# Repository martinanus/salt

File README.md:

# Proyecto SALT 

### Resumen
Este trabajo presenta el diseño e implementación de un prototipo para un sistema de aislado limitado total para formaciones ferroviarias (SAL/T) basado en un pliego de especificaciones de la empresa Trenes Argentinos Operaciones y en una primera versión del prototipo realizado anteriormente en el contexto del Grupo de Investigación en Calidad y Seguridad de las Aplicaciones Ferroviarias (GICSAFe). En esta versión, se agregan nuevas funcionalidades, se actualiza el hardware utilizado y se mejora la portabilidad de su firmware.     

Este sistema permite aumentar la seguridad de los trenes ante una falla en alguno de sus sistemas instrumentados de seguridad interfiriendo las señales de corte de tracción y freno de emergencia de la formación y aislando el subsistema en fallo. El SAL/T considera múltiples fuentes de medición de la velocidad de la formación y la comunicación con una central operativa para determinar cómo debe intervenir estas señales críticas para llevar a la formación a un estado seguro de manera controlada.

### Diagrama en bloques del SAL/T

### Diseño del panel frontal del sistema

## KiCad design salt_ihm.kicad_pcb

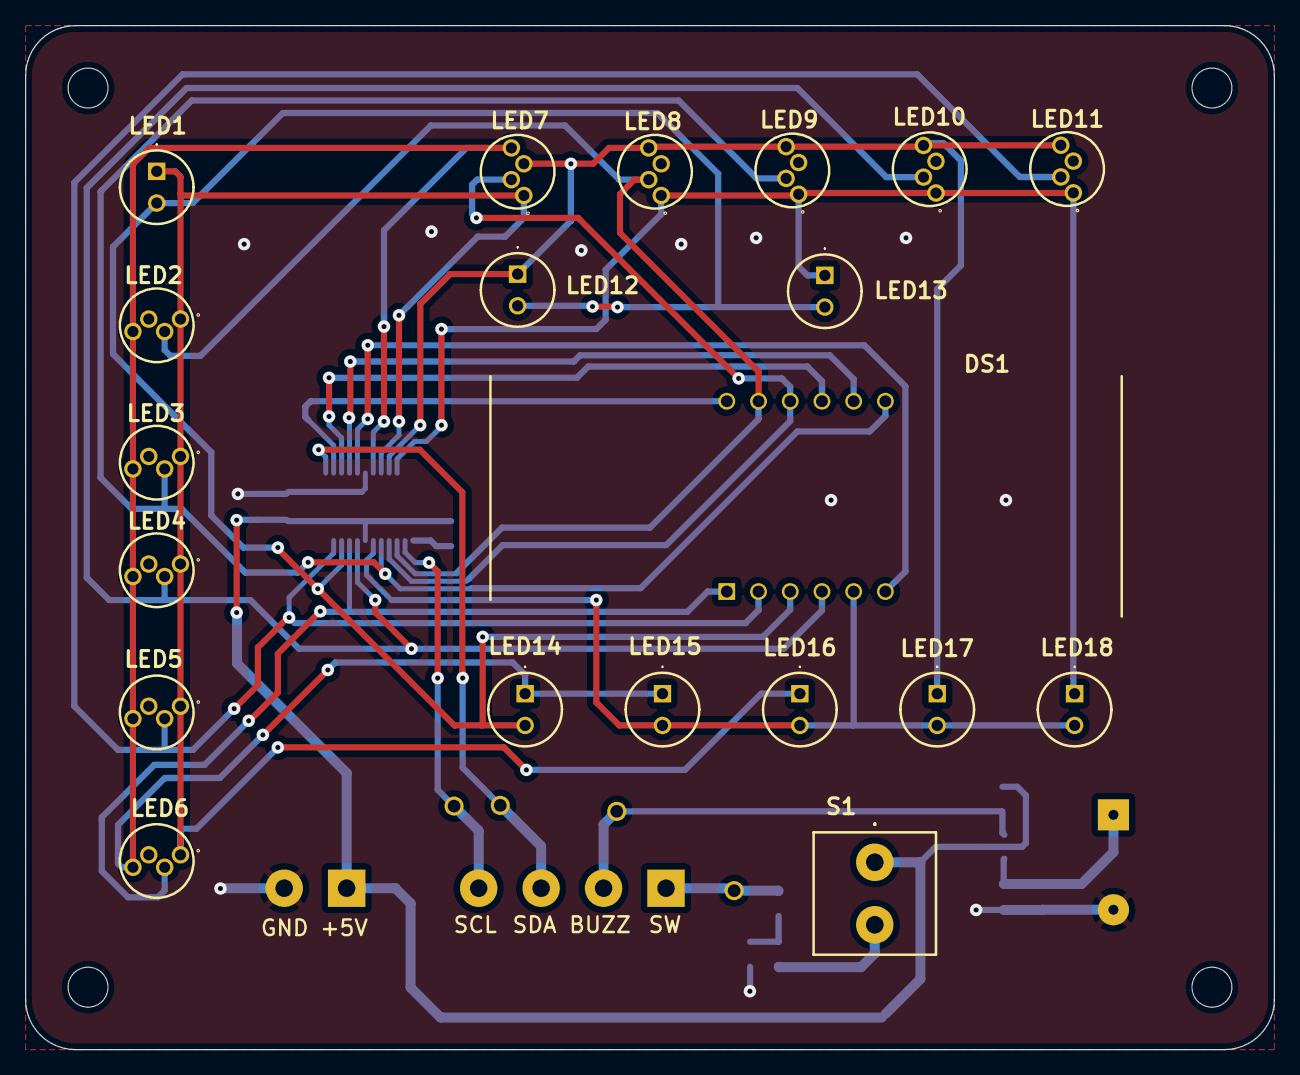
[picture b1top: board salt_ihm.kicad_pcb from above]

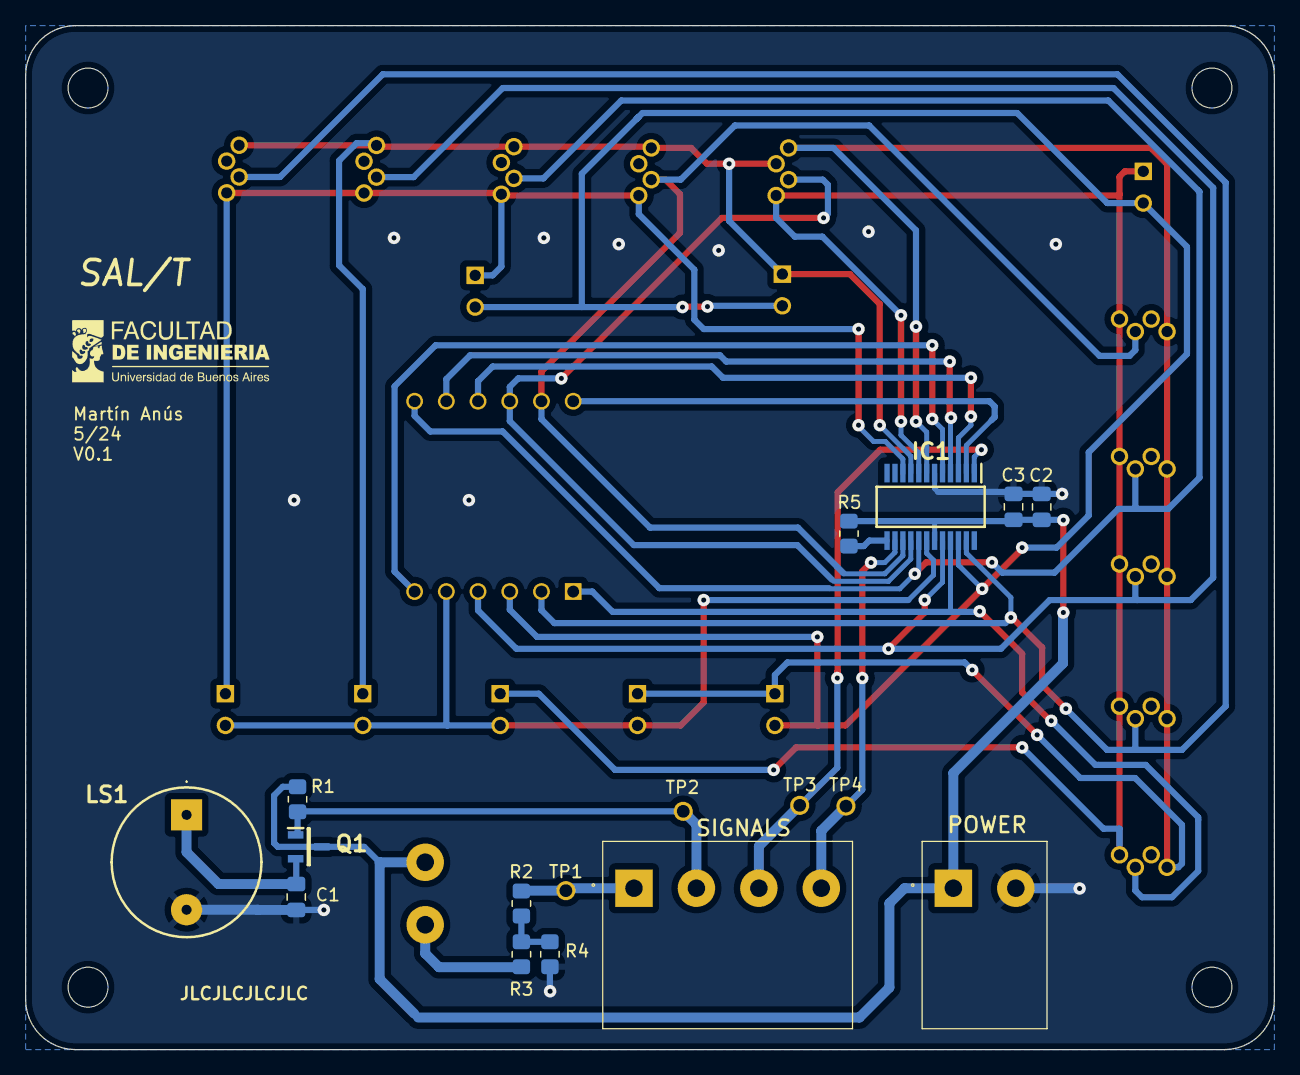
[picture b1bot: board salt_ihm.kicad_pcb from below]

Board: 2 copper layers, 100.0 x 82.0 mm, 41 parts (17 on the bottom side), 26 nets.

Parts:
C1, C2: 10uF; C_0805_2012Metric_Pad1.18x1.45mm_HandSolder
C3: 100nF; C_0805_2012Metric_Pad1.18x1.45mm_HandSolder
DS1: LTC-5723HR; DIP1524W75P254L5030H825Q12N
H1, H2, H3, H4: MountingHole; MountingHole_3.2mm_M3
IC1: AS1115-BSST; SOP64P600X175-24N
J1: 1934861
J2: 1934887
LED1, LED12, LED13, LED14, LED15, LED16, LED17, LED18: WP7113LZGCK
LED2, LED3, LED4, LED5, LED6, LED7, LED8, LED9, LED10, LED11: WP154A4SEJ3VBDZGW_CA; L-154A4SUREQBFZGEC
LS1: CEM-1205-IC; CEM1205IC
Q1: NVTR0202PLT1G; SOT96P237X111-3N
R1: 150k; R_0805_2012Metric_Pad1.20x1.40mm_HandSolder
R2: 100; R_0805_2012Metric_Pad1.20x1.40mm_HandSolder
R3, R5: 22k; R_0805_2012Metric_Pad1.20x1.40mm_HandSolder
R4: 40K2; R_0805_2012Metric_Pad1.20x1.40mm_HandSolder
S1: 1543-650-149; 1543650149
TP1, TP2, TP3, TP4: TestPoint; testpoint

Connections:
+5V: C2.1, C3.1, IC1.19 (VDD), J1.1, Q1.3 (D), R1.1, R5.1, S1.1
/A_A: DS1.11 (A_A), IC1.15 (SEGA), LED2.2 (COMMON_ANODE), LED8.2 (COMMON_ANODE)
/A_B: DS1.7 (A_B), IC1.17 (SEGB), LED3.2 (COMMON_ANODE), LED9.2 (COMMON_ANODE)
/A_C: DS1.4 (A_C), IC1.20 (SEGC), LED4.2 (COMMON_ANODE), LED10.2 (COMMON_ANODE)
/A_D: DS1.2 (A_D), IC1.23 (SEGD), LED5.2 (COMMON_ANODE), LED11.2 (COMMON_ANODE)
/A_DP: DS1.3 (A_D.P.), IC1.22 (SEGDP), LED1.2 (A), LED12.2 (A), LED13.2 (A), LED14.2 (A)
/A_E: DS1.1 (A_E), IC1.21 (SEG_E), LED6.2 (COMMON_ANODE)
/A_F: DS1.10 (A_F), IC1.16 (SEGF), LED7.2 (COMMON_ANODE)
/A_G: DS1.5 (A_G), IC1.18 (SEGG), LED15.2 (A), LED16.2 (A), LED17.2 (A), LED18.2 (A)
/BUZZER_C: J2.2, Q1.1 (G), R1.2, TP2.1
/CC_0: DS1.12 (COMMON_K_(DIGIT_1)), IC1.2 (DIG0)
/CC_1: DS1.9 (COMMON_K_(DIGIT_2)), IC1.3 (DIG1)
/CC_2: DS1.8 (COMMON_K_(DIGIT_3)), IC1.4 (DIG2)
/CC_3: DS1.6 (COMMON_K_(DIGIT_4)), IC1.5 (DIG3)
/CC_4: IC1.7 (DIG4), LED2.4 (GREEN_CATHODE), LED3.4 (GREEN_CATHODE), LED4.4 (GREEN_CATHODE), LED5.4 (GREEN_CATHODE), LED6.4 (GREEN_CATHODE), LED7.4 (GREEN_CATHODE), LED14.1 (K), LED15.1 (K)
/CC_5: IC1.8 (DIG5), LED1.1 (K), LED2.1 (RED_CATHODE), LED3.1 (RED_CATHODE), LED4.1 (RED_CATHODE), LED5.1 (RED_CATHODE), LED6.1 (RED_CATHODE), LED7.1 (RED_CATHODE), LED16.1 (K)
/CC_6: IC1.9 (DIG6), LED7.3 (BLUE_CATHODE), LED8.4 (GREEN_CATHODE), LED9.4 (GREEN_CATHODE), LED10.4 (GREEN_CATHODE), LED11.4 (GREEN_CATHODE), LED12.1 (K), LED17.1 (K)
/CC_7: IC1.10 (DIG7), LED8.1 (RED_CATHODE), LED9.1 (RED_CATHODE), LED10.1 (RED_CATHODE), LED11.1 (RED_CATHODE), LED13.1 (K), LED18.1 (K)
/CHOP_SEL: J2.1, R2.1, TP1.1
/SCL: IC1.14 (SCL), J2.4, TP4.1
/SDA: IC1.1 (SDA), J2.3, TP3.1
GND: C1.1, C2.2, C3.2, IC1.6 (GND), J1.2, LS1.2, R4.1
unnamed: C1.2, LS1.1, Q1.2 (S)
unnamed: IC1.13 (ISET), R5.2
unnamed: R2.2, R3.2, R4.2
unnamed: R3.1, S1.2

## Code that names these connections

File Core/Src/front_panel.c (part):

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    uint8_t D5_B = extractBit(SIS_leds[2], 1); // LED9_GREEN  - CC_6 - A_B  - SIS_3
    uint8_t D4_C = extractBit(SIS_leds[3], 1); // LED10_GREEN - CC_6 - A_C  - SIS_4
    uint8_t D3_D = extractBit(SIS_leds[4], 1); // LED11_GREEN - CC_6 - A_D  - SIS_5
    uint8_t D2_E = 0;                          // NC          - CC_6 - A_E  - NC
    uint8_t D1_F = extractBit(SIS_leds[0], 0); // LED7_BLUE   - CC_6 - A_F  - SIS_1-->ZONA
    uint8_t D0_G = chop_profile_leds[3];       // LED17       - CC_6 - A_G  - CHOP_4

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    uint8_t D5_B = extractBit(SIS_leds[2], 2); // LED9_RED  - CC_7 - A_B  - SIS_3
    uint8_t D4_C = extractBit(SIS_leds[3], 2); // LED10_RED - CC_7 - A_C  - SIS_4
    uint8_t D3_D = extractBit(SIS_leds[4], 2); // LED11_RED - CC_7 - A_D  - SIS_5
    uint8_t D2_E = 0;                          // NC        - CC_7 - A_E  - NC
    uint8_t D1_F = 0;                          // NC        - CC_7 - A_F  - NC
    uint8_t D0_G = chop_profile_leds[4];       // LED18     - CC_7 - A_G  - CHOP_5

    uint8_t vars[8] = {D0_G, D1_F, D2_E, D3_D, D4_C, D5_B, D6_A, D7_DP};
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
    if (buzzer_state == BUZZER_OFF)
    {
        HAL_GPIO_WritePin(BUZZER_C_GPIO_Port, BUZZER_C_Pin, 0);
        HAL_GPIO_WritePin(LD2_GPIO_Port, LD2_Pin, 0);
    }
    else if (buzzer_state == BUZZER_ON_CONTINUOS)
    {
        HAL_GPIO_WritePin(BUZZER_C_GPIO_Port, BUZZER_C_Pin, 1);
        HAL_GPIO_WritePin(LD2_GPIO_Port, LD2_Pin, 1);
    }
    else if (buzzer_state == BUZZER_ON_INTERMITENT)
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        currentMillis = HAL_GetTick();
        if (currentMillis - buzzer_toggle_ms > BUZZER_SOUND_PERIOD_S * 1000)
        {
            HAL_GPIO_TogglePin(BUZZER_C_GPIO_Port, BUZZER_C_Pin);
            HAL_GPIO_TogglePin(LD2_GPIO_Port, LD2_Pin);

            buzzer_toggle_ms = currentMillis;
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
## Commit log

2024-06-28 freeRTOS working example
2024-06-28 adc working example
2024-06-28 gps working example
2024-06-28 sd working example
2024-06-28 wifi working example
2024-06-28 integration working example
2024-06-28 first hardware principal reviewed and manufactured
2024-06-28 first hardware ihm reviewed and manufactured
2024-07-08 improves uart bidirectional communication
2024-07-08 integrates switch read, chop button int and refactor code
2024-07-08 clean build files
2024-07-28 led driver working example
2024-07-28 refactor: modularize led driver and define regs and values
2024-07-31 adds some address macros
2024-07-31 includes led_driver logic and communication
2024-07-31 working example
2024-07-31 handle salt mode transitions structure
2024-08-05 maps states to leds variables
2024-08-05 implements transition functs
2024-08-10 adds GPS module reset function
2024-08-10 adds testing relay function
2024-08-11 ads rs485 direction pin
2024-08-11 includes rs485 reading
2024-08-11 update relay enums for clarity
2024-08-11 includes relay combination states for critical signals
2024-08-15 includes critical signals setting and chop profiles timing
2024-08-18 control register relays
2024-08-18 log events when state changed
2024-08-18 includes RTC timestamps on logs
2024-08-21 use same main routine for all modes
2024-08-21 adds esp32 worjing examples
2024-08-21 retransmit datetime every 10s
2024-08-21 salt data in Serial2 pins
2024-08-21 update RTC clock from esp32 wifi messages
2024-08-25 includes RS485 reception logic
2024-08-27 display dash no speed and hide left zeros
2024-08-27 adds speed read validity time logic
2024-08-27 format user files in C style
2024-08-27 format h files
2024-08-28 read current zone from gps coordinates
2024-08-28 adds distance calculation from gps coordinates
2024-08-28 refactor speed and chop profiles for configuration
2024-08-28 allws updating speed, chop profile and command validity parameters via remote command
2024-08-28 apply command expiration
2024-08-30 includes remote salt_mode commands
2024-08-30 buzzer on intermitent in Limitado mode
2024-08-30 adds log download logic
2024-08-31 fix gps calculations
2024-08-31 fixes after commands testing
2024-08-31 implement hasler frame detection
2024-08-31 fix clearing buffer
2024-09-01 improves command receive after mqtt testing
2024-09-04 esp checks for multiple network connection
2024-09-04 adds mqtt client simulating central operativa
2024-09-04 adds ID responde in remote commands
2024-09-06 transmit ACK in separated topic
2024-09-06 adds separated topic for ACK
2024-09-06 transmit ACK msg in a different topic
2024-09-06 log status with labels
2024-09-06 adds report status period config and transmit
2024-09-06 adds STATUS topic for periodic salt report
2024-09-06 set different profile speeds according to zone and configurables
2024-09-06 activates break 30s when entering in MODO_LIMITADO without speed reference
2024-09-07 uses relay measurements to force internal error status and restaure normal mode
2024-09-07 REFACTOR: functions separated in different files sharing global variables
2024-09-08 regenerates ST code format
2024-09-11 restore adc callback
2024-09-11 first working SALT with freeRTOS version
2024-09-11 refactor gps lecture
2024-09-11 refactor comunication rx handles
2024-09-12 refactor: encapsulat variables and prototypes in files
2024-09-12 restore gpio interruption callback
2024-09-13 addas random osDelay for avoiding synch in tasks
2024-09-13 adds comm task for processing rx data with semaphore
2024-09-15 fix speed config command processing
2024-09-15 fix bad msg processing
2024-09-15 Update README.md
    - Agrega links a branches
    - Agrega diagrama en bloque del sistema
    - Agrega diseño del panel frontal
2024-10-27 drives buzzer
2024-11-01 adds testing speed profiles
2024-11-01 includes hardware files
2024-11-01 include firmware files
2024-11-01 update README description
2024-11-18 docs: improve informe final after revision on version v0.1
2024-11-24 docs: improve informe final after v0.2 revision
2024-11-24 docs: remove descripcion conceptual
2024-11-25 docs: last review informe final
2024-11-25 docs: informe final rename pages
